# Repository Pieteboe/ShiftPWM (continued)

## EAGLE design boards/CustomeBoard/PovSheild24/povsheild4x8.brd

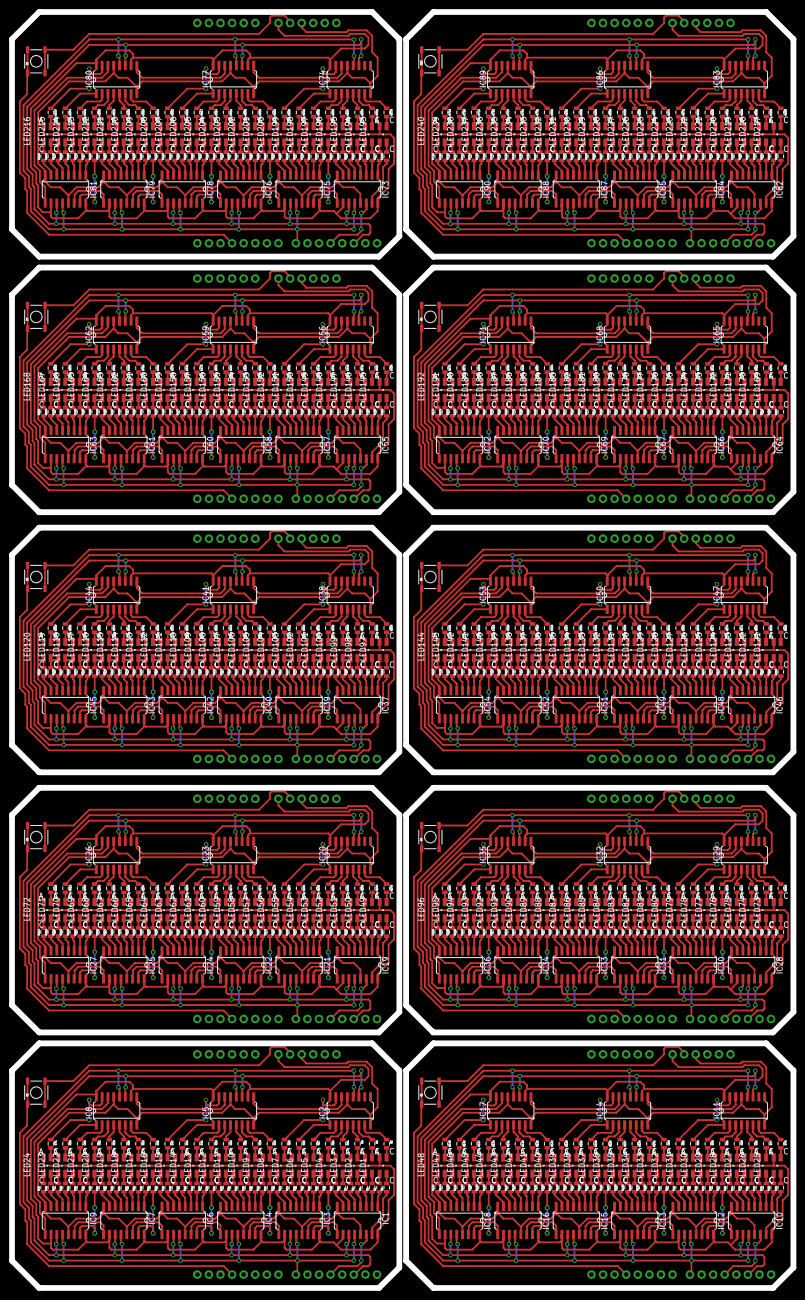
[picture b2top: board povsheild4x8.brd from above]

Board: 2 copper layers, 171.2 x 279.6 mm, 1070 parts (0 on the bottom side), 1580 nets.

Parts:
IC1, IC2, IC3, IC4, IC5, IC6, IC7, IC8, IC9, IC10, IC11, IC12, IC13, IC14, IC15, IC16, IC17, IC18, IC19, IC20, IC21, IC22, IC23, IC24, IC25, IC26, IC27, IC28, IC29, IC30, IC31, IC32, IC33, IC34, IC35, IC36, IC37, IC38, IC39, IC40, IC41, IC42, IC43, IC44, IC45, IC46, IC47, IC48, IC49, IC50, IC51, IC52, IC53, IC54, IC55, IC56, IC57, IC58, IC59, IC60, IC61, IC62, IC63, IC64, IC65, IC66, IC67, IC68, IC69, IC70, IC71, IC72, IC73, IC74, IC75, IC76, IC77, IC78, IC79, IC80, IC81, IC82, IC83, IC84, IC85, IC86, IC87, IC88, IC89, IC90: 74HC595D; SO16
LED1, LED2, LED3, LED4, LED5, LED6, LED7, LED8, LED9, LED10, LED11, LED12, LED13, LED14, LED15, LED16, LED17, LED18, LED19, LED20, LED21, LED22, LED23, LED24, LED25, LED26, LED27, LED28, LED29, LED30, LED31, LED32, LED33, LED34, LED35, LED36, LED37, LED38, LED39, LED40, LED41, LED42, LED43, LED44, LED45, LED46, LED47, LED48, LED49, LED50, LED51, LED52, LED53, LED54, LED55, LED56, LED57, LED58, LED59, LED60, LED61, LED62, LED63, LED64, LED65, LED66, LED67, LED68, LED69, LED70, LED71, LED72, LED73, LED74, LED75, LED76, LED77, LED78, LED79, LED80, LED81, LED82, LED83, LED84, LED85, LED86, LED87, LED88, LED89, LED90, LED91, LED92, LED93, LED94, LED95, LED96, LED97, LED98, LED99, LED100, LED101, LED102, LED103, LED104, LED105, LED106, LED107, LED108, LED109, LED110, LED111, LED112, LED113, LED114, LED115, LED116, LED117, LED118, LED119, LED120, LED121, LED122, LED123, LED124, LED125, LED126, LED127, LED128, LED129, LED130, LED131, LED132, LED133, LED134, LED135, LED136, LED137, LED138, LED139, LED140, LED141, LED142, LED143, LED144, LED145, LED146, LED147, LED148, LED149, LED150, LED151, LED152, LED153, LED154, LED155, LED156, LED157, LED158, LED159, LED160, LED161, LED162, LED163, LED164, LED165, LED166, LED167, LED168, LED169, LED170, LED171, LED172, LED173, LED174, LED175, LED176, LED177, LED178, LED179, LED180, LED181, LED182, LED183, LED184, LED185, LED186, LED187, LED188, LED189, LED190, LED191, LED192, LED193, LED194, LED195, LED196, LED197, LED198, LED199, LED200, LED201, LED202, LED203, LED204, LED205, LED206, LED207, LED208, LED209, LED210, LED211, LED212, LED213, LED214, LED215, LED216, LED217, LED218, LED219, LED220, LED221, LED222, LED223, LED224, LED225, LED226, LED227, LED228, LED229, LED230, LED231, LED232, LED233, LED234, LED235, LED236, LED237, LED238, LED239, LED240: P-LCC-4
R1, R2, R3, R4, R5, R6, R7, R8, R9, R10, R11, R12, R13, R14, R15, R16, R17, R18, R19, R20, R21, R22, R23, R24, R25, R26, R27, R28, R29, R30, R31, R32, R33, R34, R35, R36, R37, R38, R39, R40, R41, R42, R43, R44, R45, R46, R47, R48, R49, R50, R51, R52, R53, R54, R55, R56, R57, R58, R59, R60, R61, R62, R63, R64, R65, R66, R67, R68, R69, R70, R71, R72, R73, R74, R75, R76, R77, R78, R79, R80, R81, R82, R83, R84, R85, R86, R87, R88, R89, R90, R91, R92, R93, R94, R95, R96, R97, R98, R99, R100, R101, R102, R103, R104, R105, R106, R107, R108, R109, R110, R111, R112, R113, R114, R115, R116, R117, R118, R119, R120, R121, R122, R123, R124, R125, R126, R127, R128, R129, R130, R131, R132, R133, R134, R135, R136, R137, R138, R139, R140, R141, R142, R143, R144, R145, R146, R147, R148, R149, R150, R151, R152, R153, R154, R155, R156, R157, R158, R159, R160, R161, R162, R163, R164, R165, R166, R167, R168, R169, R170, R171, R172, R173, R174, R175, R176, R177, R178, R179, R180, R181, R182, R183, R184, R185, R186, R187, R188, R189, R190, R191, R192, R193, R194, R195, R196, R197, R198, R199, R200, R201, R202, R203, R204, R205, R206, R207, R208, R209, R210, R211, R212, R213, R214, R215, R216, R217, R218, R219, R220, R221, R222, R223, R224, R225, R226, R227, R228, R229, R230, R231, R232, R233, R234, R235, R236, R237, R238, R239, R240, R241, R242, R243, R244, R245, R246, R247, R248, R249, R250, R251, R252, R253, R254, R255, R256, R257, R258, R259, R260, R261, R262, R263, R264, R265, R266, R267, R268, R269, R270, R271, R272, R273, R274, R275, R276, R277, R278, R279, R280, R281, R282, R283, R284, R285, R286, R287, R288, R289, R290, R291, R292, R293, R294, R295, R296, R297, R298, R299, R300, R301, R302, R303, R304, R305, R306, R307, R308, R309, R310, R311, R312, R313, R314, R315, R316, R317, R318, R319, R320, R321, R322, R323, R324, R325, R326, R327, R328, R329, R330, R331, R332, R333, R334, R335, R336, R337, R338, R339, R340, R341, R342, R343, R344, R345, R346, R347, R348, R349, R350, R351, R352, R353, R354, R355, R356, R357, R358, R359, R360, R361, R362, R363, R364, R365, R366, R367, R368, R369, R370, R371, R372, R373, R374, R375, R376, R377, R378, R379, R380, R381, R382, R383, R384, R385, R386, R387, R388, R389, R390, R391, R392, R393, R394, R395, R396, R397, R398, R399, R400, R401, R402, R403, R404, R405, R406, R407, R408, R409, R410, R411, R412, R413, R414, R415, R416, R417, R418, R419, R420, R421, R422, R423, R424, R425, R426, R427, R428, R429, R430, R431, R432, R433, R434, R435, R436, R437, R438, R439, R440, R441, R442, R443, R444, R445, R446, R447, R448, R449, R450, R451, R452, R453, R454, R455, R456, R457, R458, R459, R460, R461, R462, R463, R464, R465, R466, R467, R468, R469, R470, R471, R472, R473, R474, R475, R476, R477, R478, R479, R480, R481, R482, R483, R484, R485, R486, R487, R488, R489, R490, R491, R492, R493, R494, R495, R496, R497, R498, R499, R500, R501, R502, R503, R504, R505, R506, R507, R508, R509, R510, R511, R512, R513, R514, R515, R516, R517, R518, R519, R520, R521, R522, R523, R524, R525, R526, R527, R528, R529, R530, R531, R532, R533, R534, R535, R536, R537, R538, R539, R540, R541, R542, R543, R544, R545, R546, R547, R548, R549, R550, R551, R552, R553, R554, R555, R556, R557, R558, R559, R560, R561, R562, R563, R564, R565, R566, R567, R568, R569, R570, R571, R572, R573, R574, R575, R576, R577, R578, R579, R580, R581, R582, R583, R584, R585, R586, R587, R588, R589, R590, R591, R592, R593, R594, R595, R596, R597, R598, R599, R600, R601, R602, R603, R604, R605, R606, R607, R608, R609, R610, R611, R612, R613, R614, R615, R616, R617, R618, R619, R620, R621, R622, R623, R624, R625, R626, R627, R628, R629, R630, R631, R632, R633, R634, R635, R636, R637, R638, R639, R640, R641, R642, R643, R644, R645, R646, R647, R648, R649, R650, R651, R652, R653, R654, R655, R656, R657, R658, R659, R660, R661, R662, R663, R664, R665, R666, R667, R668, R669, R670, R671, R672, R673, R674, R675, R676, R677, R678, R679, R680, R681, R682, R683, R684, R685, R686, R687, R688, R689, R690, R691, R692, R693, R694, R695, R696, R697, R698, R699, R700, R701, R702, R703, R704, R705, R706, R707, R708, R709, R710, R711, R712, R713, R714, R715, R716, R717, R718, R719, R720: 0805
S1, S2, S3, S4, S5, S6, S7, S8, S9, S10: TACTILE_SWITCH_SMD
U1, U2, U3, U4, U5, U6, U7, U8, U9, U10: ARDUINO_SHIELDNO_SILK; DUEMILANOVE_VIAS

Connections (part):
GND: IC1.8, IC1.13, IC2.8, IC2.13, IC3.8, IC3.13, IC4.8, IC4.13, IC5.8, IC5.13, IC6.8, IC6.13, IC7.8, IC7.13, IC8.8, IC8.13, IC9.8, IC9.13, S2.3, S2.4, U1.GND@0, U1.GND@1
GND1: IC10.8, IC10.13, IC11.8, IC11.13, IC12.8, IC12.13, IC13.8, IC13.13, IC14.8, IC14.13, IC15.8, IC15.13, IC16.8, IC16.13, IC17.8, IC17.13, IC18.8, IC18.13, S1.3, S1.4, U2.GND@0, U2.GND@1
GND2: IC19.8, IC19.13, IC20.8, IC20.13, IC21.8, IC21.13, IC22.8, IC22.13, IC23.8, IC23.13, IC24.8, IC24.13, IC25.8, IC25.13, IC26.8, IC26.13, IC27.8, IC27.13, S3.3, S3.4, U3.GND@0, U3.GND@1
GND3: IC28.8, IC28.13, IC29.8, IC29.13, IC30.8, IC30.13, IC31.8, IC31.13, IC32.8, IC32.13, IC33.8, IC33.13, IC34.8, IC34.13, IC35.8, IC35.13, IC36.8, IC36.13, S4.3, S4.4, U4.GND@0, U4.GND@1
GND4: IC37.8, IC37.13, IC38.8, IC38.13, IC39.8, IC39.13, IC40.8, IC40.13, IC41.8, IC41.13, IC42.8, IC42.13, IC43.8, IC43.13, IC44.8, IC44.13, IC45.8, IC45.13, S5.3, S5.4, U5.GND@0, U5.GND@1
GND5: IC46.8, IC46.13, IC47.8, IC47.13, IC48.8, IC48.13, IC49.8, IC49.13, IC50.8, IC50.13, IC51.8, IC51.13, IC52.8, IC52.13, IC53.8, IC53.13, IC54.8, IC54.13, S6.3, S6.4, U6.GND@0, U6.GND@1
GND6: IC55.8, IC55.13, IC56.8, IC56.13, IC57.8, IC57.13, IC58.8, IC58.13, IC59.8, IC59.13, IC60.8, IC60.13, IC61.8, IC61.13, IC62.8, IC62.13, IC63.8, IC63.13, S7.3, S7.4, U7.GND@0, U7.GND@1
GND7: IC64.8, IC64.13, IC65.8, IC65.13, IC66.8, IC66.13, IC67.8, IC67.13, IC68.8, IC68.13, IC69.8, IC69.13, IC70.8, IC70.13, IC71.8, IC71.13, IC72.8, IC72.13, S8.3, S8.4, U8.GND@0, U8.GND@1
GND8: IC73.8, IC73.13, IC74.8, IC74.13, IC75.8, IC75.13, IC76.8, IC76.13, IC77.8, IC77.13, IC78.8, IC78.13, IC79.8, IC79.13, IC80.8, IC80.13, IC81.8, IC81.13, S9.3, S9.4, U9.GND@0, U9.GND@1
GND9: IC82.8, IC82.13, IC83.8, IC83.13, IC84.8, IC84.13, IC85.8, IC85.13, IC86.8, IC86.13, IC87.8, IC87.13, IC88.8, IC88.13, IC89.8, IC89.13, IC90.8, IC90.13, S10.3, S10.4, U10.GND@0, U10.GND@1
LATCH: IC1.12, IC2.12, IC3.12, IC4.12, IC5.12, IC6.12, IC7.12, IC8.12, IC9.12, U1.D8
LATCH1: IC10.12, IC11.12, IC12.12, IC13.12, IC14.12, IC15.12, IC16.12, IC17.12, IC18.12, U2.D8
LATCH2: IC19.12, IC20.12, IC21.12, IC22.12, IC23.12, IC24.12, IC25.12, IC26.12, IC27.12, U3.D8
LATCH3: IC28.12, IC29.12, IC30.12, IC31.12, IC32.12, IC33.12, IC34.12, IC35.12, IC36.12, U4.D8
LATCH4: IC37.12, IC38.12, IC39.12, IC40.12, IC41.12, IC42.12, IC43.12, IC44.12, IC45.12, U5.D8
LATCH5: IC46.12, IC47.12, IC48.12, IC49.12, IC50.12, IC51.12, IC52.12, IC53.12, IC54.12, U6.D8
LATCH6: IC55.12, IC56.12, IC57.12, IC58.12, IC59.12, IC60.12, IC61.12, IC62.12, IC63.12, U7.D8
LATCH7: IC64.12, IC65.12, IC66.12, IC67.12, IC68.12, IC69.12, IC70.12, IC71.12, IC72.12, U8.D8
LATCH8: IC73.12, IC74.12, IC75.12, IC76.12, IC77.12, IC78.12, IC79.12, IC80.12, IC81.12, U9.D8
LATCH9: IC82.12, IC83.12, IC84.12, IC85.12, IC86.12, IC87.12, IC88.12, IC89.12, IC90.12, U10.D8
unnamed: IC1.15, R3.1
unnamed: IC1.1, R1.1
unnamed: IC1.2, R6.1
unnamed: IC1.3, R4.1
unnamed: IC1.4, R9.1
unnamed: IC1.5, R7.1
unnamed: IC1.6, R12.1
unnamed: IC1.7, R10.1
unnamed: LED1.C@1, R1.2
unnamed: LED1.C@3, R2.2
unnamed: LED1.C@4, R3.2
unnamed: LED2.C@1, R4.2
unnamed: LED2.C@3, R5.2
unnamed: LED2.C@4, R6.2
unnamed: LED3.C@1, R7.2
unnamed: LED3.C@3, R8.2
unnamed: LED3.C@4, R9.2
unnamed: LED4.C@1, R10.2
unnamed: IC3.15, R15.1
unnamed: IC3.1, R13.1
unnamed: LED4.C@3, R11.2
unnamed: IC3.2, R18.1
unnamed: IC3.3, R16.1
unnamed: IC3.4, R21.1
unnamed: IC3.5, R19.1
unnamed: IC3.6, R24.1
unnamed: IC3.7, R22.1
unnamed: LED4.C@4, R12.2
unnamed: LED5.C@1, R13.2
unnamed: LED5.C@3, R14.2
unnamed: LED5.C@4, R15.2
unnamed: LED6.C@1, R16.2
unnamed: LED6.C@3, R17.2
unnamed: LED6.C@4, R18.2
unnamed: IC2.15, R23.1
unnamed: IC2.1, R20.1
unnamed: LED7.C@1, R19.2
unnamed: IC2.2, R17.1
unnamed: LED7.C@3, R20.2
unnamed: IC2.3, R14.1
unnamed: LED7.C@4, R21.2
unnamed: IC2.4, R11.1
unnamed: IC2.5, R8.1
unnamed: IC2.6, R5.1
unnamed: IC2.7, R2.1
unnamed: LED8.C@1, R22.2
unnamed: LED8.C@3, R23.2
unnamed: LED8.C@4, R24.2
unnamed: IC4.15, R27.1
unnamed: IC4.1, R25.1
unnamed: IC4.2, R30.1
unnamed: IC4.3, R28.1
unnamed: IC4.4, R33.1
unnamed: IC4.5, R31.1
unnamed: IC4.6, R36.1
unnamed: IC4.7, R34.1
unnamed: LED9.C@1, R25.2
unnamed: LED9.C@3, R26.2
unnamed: LED9.C@4, R27.2
unnamed: LED10.C@1, R28.2
unnamed: LED10.C@3, R29.2
unnamed: LED10.C@4, R30.2
unnamed: LED11.C@1, R31.2
unnamed: LED11.C@3, R32.2
unnamed: LED11.C@4, R33.2
unnamed: LED12.C@1, R34.2
unnamed: IC5.15, R47.1
unnamed: IC5.1, R44.1
unnamed: LED12.C@3, R35.2
unnamed: IC5.2, R41.1
unnamed: IC5.3, R38.1
unnamed: IC5.4, R35.1
unnamed: IC5.5, R32.1
unnamed: IC5.6, R29.1
unnamed: IC5.7, R26.1
unnamed: LED12.C@4, R36.2
unnamed: LED13.C@1, R37.2
unnamed: LED13.C@3, R38.2
unnamed: LED13.C@4, R39.2
unnamed: LED14.C@1, R40.2
unnamed: LED14.C@3, R41.2
unnamed: LED14.C@4, R42.2
unnamed: IC6.15, R39.1
unnamed: IC6.1, R37.1
unnamed: LED15.C@1, R43.2
unnamed: IC6.2, R42.1
unnamed: LED15.C@3, R44.2
unnamed: IC6.3, R40.1
unnamed: LED15.C@4, R45.2
unnamed: IC6.4, R45.1
unnamed: IC6.5, R43.1
unnamed: IC6.6, R48.1
unnamed: IC6.7, R46.1
unnamed: LED16.C@1, R46.2
unnamed: LED16.C@3, R47.2
unnamed: LED16.C@4, R48.2
unnamed: LED25.C@1, R73.2
unnamed: LED25.C@3, R74.2
unnamed: LED25.C@4, R75.2
unnamed: LED26.C@1, R76.2
unnamed: LED26.C@3, R77.2
unnamed: LED26.C@4, R78.2
unnamed: LED27.C@1, R79.2
unnamed: LED27.C@3, R80.2
unnamed: LED17.C@1, R49.2
unnamed: LED17.C@3, R50.2
unnamed: LED17.C@4, R51.2
unnamed: LED18.C@1, R52.2
unnamed: LED18.C@3, R53.2
unnamed: LED18.C@4, R54.2
unnamed: LED19.C@1, R55.2
unnamed: LED19.C@3, R56.2
unnamed: LED19.C@4, R57.2
unnamed: LED20.C@1, R58.2
unnamed: LED27.C@4, R81.2
unnamed: LED28.C@1, R82.2
unnamed: LED20.C@3, R59.2
unnamed: LED28.C@3, R83.2
unnamed: LED28.C@4, R84.2
unnamed: LED29.C@1, R85.2
unnamed: LED29.C@3, R86.2
unnamed: LED29.C@4, R87.2
unnamed: LED30.C@1, R88.2
unnamed: LED20.C@4, R60.2
unnamed: LED21.C@1, R61.2
unnamed: LED21.C@3, R62.2
unnamed: LED21.C@4, R63.2
unnamed: LED22.C@1, R64.2
unnamed: LED22.C@3, R65.2
unnamed: LED22.C@4, R66.2
unnamed: LED30.C@3, R89.2
unnamed: LED30.C@4, R90.2
unnamed: LED23.C@1, R67.2
unnamed: LED31.C@1, R91.2
unnamed: LED23.C@3, R68.2
unnamed: LED31.C@3, R92.2
unnamed: LED23.C@4, R69.2
unnamed: LED31.C@4, R93.2
unnamed: LED32.C@1, R94.2
unnamed: LED32.C@3, R95.2
unnamed: LED32.C@4, R96.2
unnamed: LED24.C@1, R70.2
unnamed: LED24.C@3, R71.2
unnamed: LED24.C@4, R72.2
unnamed: IC7.15, R51.1
unnamed: IC7.1, R49.1
unnamed: IC7.2, R54.1
unnamed: IC7.3, R52.1
unnamed: IC7.4, R57.1
unnamed: IC7.5, R55.1
unnamed: IC7.6, R60.1
unnamed: IC7.7, R58.1
unnamed: LED33.C@1, R97.2
unnamed: LED33.C@3, R98.2
unnamed: LED33.C@4, R99.2
unnamed: LED34.C@1, R100.2
unnamed: LED34.C@3, R101.2
unnamed: LED34.C@4, R102.2
unnamed: LED35.C@1, R103.2
unnamed: LED35.C@3, R104.2
unnamed: LED35.C@4, R105.2
unnamed: LED36.C@1, R106.2
unnamed: IC8.15, R71.1
unnamed: IC8.1, R68.1
unnamed: LED36.C@3, R107.2
unnamed: IC8.2, R65.1
unnamed: IC8.3, R62.1
unnamed: IC8.4, R59.1
unnamed: IC8.5, R56.1
unnamed: IC8.6, R53.1
unnamed: IC8.7, R50.1
unnamed: LED36.C@4, R108.2
unnamed: LED37.C@1, R109.2
unnamed: LED37.C@3, R110.2
unnamed: LED37.C@4, R111.2
unnamed: LED38.C@1, R112.2
unnamed: LED38.C@3, R113.2
unnamed: LED38.C@4, R114.2
unnamed: IC9.15, R63.1
unnamed: IC9.1, R61.1
unnamed: LED39.C@1, R115.2
unnamed: IC9.2, R66.1
unnamed: LED39.C@3, R116.2
unnamed: IC9.3, R64.1
unnamed: LED39.C@4, R117.2
unnamed: IC9.4, R69.1
unnamed: IC9.5, R67.1
unnamed: IC9.6, R72.1
unnamed: IC9.7, R70.1
unnamed: LED40.C@1, R118.2
unnamed: LED40.C@3, R119.2
unnamed: LED40.C@4, R120.2
unnamed: IC1.9, IC3.14
unnamed: IC3.9, IC4.14
unnamed: IC4.9, IC6.14
unnamed: IC6.9, IC7.14
unnamed: IC7.9, IC9.14
unnamed: LED41.C@1, R121.2
unnamed: LED41.C@3, R122.2
unnamed: LED41.C@4, R123.2
unnamed: IC2.14, IC5.9
unnamed: IC5.14, IC8.9
unnamed: IC8.14, IC9.9
unnamed: LED42.C@1, R124.2
unnamed: IC1.14, U1.D11
unnamed: S2.1, S2.2, U1.D3
unnamed: LED42.C@3, R125.2
unnamed: LED42.C@4, R126.2
unnamed: LED43.C@1, R127.2
unnamed: LED43.C@3, R128.2
unnamed: LED43.C@4, R129.2
unnamed: LED44.C@1, R130.2
unnamed: LED44.C@3, R131.2
unnamed: LED44.C@4, R132.2
unnamed: LED45.C@1, R133.2
unnamed: LED45.C@3, R134.2
unnamed: LED45.C@4, R135.2
unnamed: LED46.C@1, R136.2
unnamed: LED46.C@3, R137.2
unnamed: LED46.C@4, R138.2
unnamed: LED47.C@1, R139.2
unnamed: LED47.C@3, R140.2
unnamed: LED47.C@4, R141.2
unnamed: LED48.C@1, R142.2
unnamed: LED48.C@3, R143.2
unnamed: LED48.C@4, R144.2
unnamed: IC10.15, R75.1
unnamed: IC10.1, R73.1
unnamed: IC10.2, R78.1
unnamed: IC10.3, R76.1
unnamed: IC10.4, R81.1
unnamed: IC10.5, R79.1
unnamed: IC10.6, R84.1
unnamed: IC10.7, R82.1
unnamed: IC12.15, R87.1
unnamed: IC12.1, R85.1
unnamed: IC12.2, R90.1
unnamed: IC12.3, R88.1
unnamed: IC12.4, R93.1
unnamed: IC12.5, R91.1
unnamed: IC12.6, R96.1
unnamed: IC12.7, R94.1
unnamed: IC11.15, R95.1
unnamed: IC11.1, R92.1
unnamed: IC11.2, R89.1
unnamed: IC11.3, R86.1
unnamed: IC11.4, R83.1
unnamed: IC11.5, R80.1
unnamed: IC11.6, R77.1
unnamed: IC11.7, R74.1
unnamed: IC13.15, R99.1
unnamed: IC13.1, R97.1
unnamed: IC13.2, R102.1
unnamed: IC13.3, R100.1
unnamed: IC13.4, R105.1
unnamed: IC13.5, R103.1
unnamed: IC13.6, R108.1
unnamed: IC13.7, R106.1
unnamed: IC14.15, R119.1
unnamed: IC14.1, R116.1
unnamed: IC14.2, R113.1
unnamed: IC14.3, R110.1
unnamed: IC14.4, R107.1
unnamed: IC14.5, R104.1
unnamed: IC14.6, R101.1
unnamed: IC14.7, R98.1
unnamed: IC15.15, R111.1
unnamed: IC15.1, R109.1
unnamed: IC15.2, R114.1
unnamed: IC15.3, R112.1
unnamed: IC15.4, R117.1
unnamed: IC15.5, R115.1
unnamed: IC15.6, R120.1
unnamed: IC15.7, R118.1
unnamed: IC16.15, R123.1
unnamed: IC16.1, R121.1
unnamed: IC16.2, R126.1
unnamed: IC16.3, R124.1
unnamed: IC16.4, R129.1
unnamed: IC16.5, R127.1
unnamed: IC16.6, R132.1
unnamed: IC16.7, R130.1
unnamed: IC18.15, R135.1
unnamed: IC18.1, R133.1
unnamed: IC18.2, R138.1
unnamed: IC18.3, R136.1
unnamed: IC18.4, R141.1
unnamed: IC18.5, R139.1
unnamed: IC18.6, R144.1
unnamed: IC18.7, R142.1
unnamed: IC17.15, R143.1
unnamed: IC17.1, R140.1
unnamed: IC17.2, R137.1
unnamed: IC17.3, R134.1
unnamed: IC17.4, R131.1
unnamed: IC17.5, R128.1
unnamed: IC17.6, R125.1
unnamed: IC17.7, R122.1
unnamed: IC10.9, IC12.14
unnamed: IC12.9, IC13.14
unnamed: IC13.9, IC15.14
unnamed: IC15.9, IC16.14
unnamed: IC16.9, IC18.14
unnamed: IC17.14, IC18.9
unnamed: IC14.14, IC17.9
unnamed: IC11.14, IC14.9
unnamed: IC10.14, U2.D11
unnamed: S1.1, S1.2, U2.D3
unnamed: LED49.C@1, R145.2
unnamed: LED49.C@3, R146.2
unnamed: LED49.C@4, R147.2
unnamed: LED50.C@1, R148.2
unnamed: LED50.C@3, R149.2
unnamed: LED50.C@4, R150.2
unnamed: LED51.C@1, R151.2
unnamed: LED51.C@3, R152.2
unnamed: LED51.C@4, R153.2
unnamed: LED52.C@1, R154.2
unnamed: LED52.C@3, R155.2
unnamed: LED52.C@4, R156.2
unnamed: LED53.C@1, R157.2
unnamed: LED53.C@3, R158.2
unnamed: LED53.C@4, R159.2
unnamed: LED54.C@1, R160.2
unnamed: LED54.C@3, R161.2
unnamed: LED54.C@4, R162.2
unnamed: LED55.C@1, R163.2
unnamed: LED55.C@3, R164.2
unnamed: LED55.C@4, R165.2
unnamed: LED56.C@1, R166.2
unnamed: LED56.C@3, R167.2
unnamed: LED56.C@4, R168.2
unnamed: LED57.C@1, R169.2
unnamed: LED57.C@3, R170.2
unnamed: LED57.C@4, R171.2
unnamed: LED58.C@1, R172.2
unnamed: LED58.C@3, R173.2
unnamed: LED58.C@4, R174.2
unnamed: LED59.C@1, R175.2
unnamed: LED59.C@3, R176.2
unnamed: LED59.C@4, R177.2
unnamed: LED60.C@1, R178.2
unnamed: LED60.C@3, R179.2
unnamed: LED60.C@4, R180.2
unnamed: LED61.C@1, R181.2
unnamed: LED61.C@3, R182.2
unnamed: LED61.C@4, R183.2
unnamed: LED62.C@1, R184.2
unnamed: LED62.C@3, R185.2
unnamed: LED62.C@4, R186.2
unnamed: LED63.C@1, R187.2
unnamed: LED63.C@3, R188.2
unnamed: LED63.C@4, R189.2
unnamed: LED64.C@1, R190.2
unnamed: LED64.C@3, R191.2
unnamed: LED64.C@4, R192.2
unnamed: LED65.C@1, R193.2
unnamed: LED65.C@3, R194.2
unnamed: LED65.C@4, R195.2
unnamed: LED66.C@1, R196.2
unnamed: LED66.C@3, R197.2
unnamed: LED66.C@4, R198.2
unnamed: LED67.C@1, R199.2
unnamed: LED67.C@3, R200.2
unnamed: LED67.C@4, R201.2
unnamed: LED68.C@1, R202.2
unnamed: LED68.C@3, R203.2
unnamed: LED68.C@4, R204.2
unnamed: LED69.C@1, R205.2
unnamed: LED69.C@3, R206.2
unnamed: LED69.C@4, R207.2
unnamed: LED70.C@1, R208.2
unnamed: LED70.C@3, R209.2
unnamed: LED70.C@4, R210.2
unnamed: LED71.C@1, R211.2
unnamed: LED71.C@3, R212.2
unnamed: LED71.C@4, R213.2
unnamed: LED72.C@1, R214.2
unnamed: LED72.C@3, R215.2
unnamed: LED72.C@4, R216.2
unnamed: IC19.15, R147.1
unnamed: IC19.1, R145.1
unnamed: IC19.2, R150.1
unnamed: IC19.3, R148.1
unnamed: IC19.4, R153.1
unnamed: IC19.5, R151.1
unnamed: IC19.6, R156.1
unnamed: IC19.7, R154.1
unnamed: IC21.15, R159.1
unnamed: IC21.1, R157.1
unnamed: IC21.2, R162.1
unnamed: IC21.3, R160.1
unnamed: IC21.4, R165.1
unnamed: IC21.5, R163.1
unnamed: IC21.6, R168.1
unnamed: IC21.7, R166.1
unnamed: IC20.15, R167.1
unnamed: IC20.1, R164.1
unnamed: IC20.2, R161.1
unnamed: IC20.3, R158.1
unnamed: IC20.4, R155.1
unnamed: IC20.5, R152.1
unnamed: IC20.6, R149.1
unnamed: IC20.7, R146.1
unnamed: IC22.15, R171.1
unnamed: IC22.1, R169.1
unnamed: IC22.2, R174.1
unnamed: IC22.3, R172.1
unnamed: IC22.4, R177.1
unnamed: IC22.5, R175.1
unnamed: IC22.6, R180.1
unnamed: IC22.7, R178.1
unnamed: IC23.15, R191.1
unnamed: IC23.1, R188.1
unnamed: IC23.2, R185.1
unnamed: IC23.3, R182.1
unnamed: IC23.4, R179.1
unnamed: IC23.5, R176.1
unnamed: IC23.6, R173.1
unnamed: IC23.7, R170.1
unnamed: IC24.15, R183.1
unnamed: IC24.1, R181.1
unnamed: IC24.2, R186.1
unnamed: IC24.3, R184.1
unnamed: IC24.4, R189.1
unnamed: IC24.5, R187.1
unnamed: IC24.6, R192.1
unnamed: IC24.7, R190.1
unnamed: IC25.15, R195.1
unnamed: IC25.1, R193.1
unnamed: IC25.2, R198.1
unnamed: IC25.3, R196.1
unnamed: IC25.4, R201.1
unnamed: IC25.5, R199.1
unnamed: IC25.6, R204.1
unnamed: IC25.7, R202.1
unnamed: IC27.15, R207.1
unnamed: IC27.1, R205.1
unnamed: IC27.2, R210.1
unnamed: IC27.3, R208.1
unnamed: IC27.4, R213.1
unnamed: IC27.5, R211.1
unnamed: IC27.6, R216.1
unnamed: IC27.7, R214.1
unnamed: IC26.15, R215.1
unnamed: IC26.1, R212.1
unnamed: IC26.2, R209.1
unnamed: IC26.3, R206.1
unnamed: IC26.4, R203.1
unnamed: IC26.5, R200.1
unnamed: IC26.6, R197.1
unnamed: IC26.7, R194.1
unnamed: IC19.9, IC21.14
unnamed: IC21.9, IC22.14
unnamed: IC22.9, IC24.14
unnamed: IC24.9, IC25.14
unnamed: IC25.9, IC27.14
unnamed: IC26.14, IC27.9
unnamed: IC23.14, IC26.9
unnamed: IC20.14, IC23.9
unnamed: IC19.14, U3.D11
unnamed: S3.1, S3.2, U3.D3
unnamed: LED73.C@1, R217.2
unnamed: LED73.C@3, R218.2
unnamed: LED73.C@4, R219.2
unnamed: LED74.C@1, R220.2
unnamed: LED74.C@3, R221.2
unnamed: LED74.C@4, R222.2
unnamed: LED75.C@1, R223.2
unnamed: LED75.C@3, R224.2
unnamed: LED75.C@4, R225.2
unnamed: LED76.C@1, R226.2
unnamed: LED76.C@3, R227.2
unnamed: LED76.C@4, R228.2
unnamed: LED77.C@1, R229.2
unnamed: LED77.C@3, R230.2
unnamed: LED77.C@4, R231.2
unnamed: LED78.C@1, R232.2
unnamed: LED78.C@3, R233.2
unnamed: LED78.C@4, R234.2
unnamed: LED79.C@1, R235.2
unnamed: LED79.C@3, R236.2
unnamed: LED79.C@4, R237.2
unnamed: LED80.C@1, R238.2
unnamed: LED80.C@3, R239.2
unnamed: LED80.C@4, R240.2
unnamed: LED81.C@1, R241.2
unnamed: LED81.C@3, R242.2
unnamed: LED81.C@4, R243.2
unnamed: LED82.C@1, R244.2
unnamed: LED82.C@3, R245.2
unnamed: LED82.C@4, R246.2
unnamed: LED83.C@1, R247.2
unnamed: LED83.C@3, R248.2
unnamed: LED83.C@4, R249.2
unnamed: LED84.C@1, R250.2
unnamed: LED84.C@3, R251.2
unnamed: LED84.C@4, R252.2
unnamed: LED85.C@1, R253.2
unnamed: LED85.C@3, R254.2
unnamed: LED85.C@4, R255.2
unnamed: LED86.C@1, R256.2
unnamed: LED86.C@3, R257.2
unnamed: LED86.C@4, R258.2
unnamed: LED87.C@1, R259.2
unnamed: LED87.C@3, R260.2
unnamed: LED87.C@4, R261.2
unnamed: LED88.C@1, R262.2
unnamed: LED88.C@3, R263.2
unnamed: LED88.C@4, R264.2
unnamed: LED89.C@1, R265.2
unnamed: LED89.C@3, R266.2
unnamed: LED89.C@4, R267.2
unnamed: LED90.C@1, R268.2
unnamed: LED90.C@3, R269.2
unnamed: LED90.C@4, R270.2
unnamed: LED91.C@1, R271.2
unnamed: LED91.C@3, R272.2
unnamed: LED91.C@4, R273.2
unnamed: LED92.C@1, R274.2
unnamed: LED92.C@3, R275.2
unnamed: LED92.C@4, R276.2
unnamed: LED93.C@1, R277.2
unnamed: LED93.C@3, R278.2
unnamed: LED93.C@4, R279.2
unnamed: LED94.C@1, R280.2
unnamed: LED94.C@3, R281.2
unnamed: LED94.C@4, R282.2
unnamed: LED95.C@1, R283.2
unnamed: LED95.C@3, R284.2
unnamed: LED95.C@4, R285.2
unnamed: LED96.C@1, R286.2
unnamed: LED96.C@3, R287.2
unnamed: LED96.C@4, R288.2
unnamed: IC28.15, R219.1
unnamed: IC28.1, R217.1
unnamed: IC28.2, R222.1
unnamed: IC28.3, R220.1
unnamed: IC28.4, R225.1
unnamed: IC28.5, R223.1
unnamed: IC28.6, R228.1
unnamed: IC28.7, R226.1
unnamed: IC30.15, R231.1
unnamed: IC30.1, R229.1
unnamed: IC30.2, R234.1
unnamed: IC30.3, R232.1
unnamed: IC30.4, R237.1
unnamed: IC30.5, R235.1
unnamed: IC30.6, R240.1
unnamed: IC30.7, R238.1
unnamed: IC29.15, R239.1
unnamed: IC29.1, R236.1
unnamed: IC29.2, R233.1
unnamed: IC29.3, R230.1
unnamed: IC29.4, R227.1
unnamed: IC29.5, R224.1
unnamed: IC29.6, R221.1
unnamed: IC29.7, R218.1
unnamed: IC31.15, R243.1
unnamed: IC31.1, R241.1
unnamed: IC31.2, R246.1
unnamed: IC31.3, R244.1
unnamed: IC31.4, R249.1
unnamed: IC31.5, R247.1
unnamed: IC31.6, R252.1
unnamed: IC31.7, R250.1
unnamed: IC32.15, R263.1
unnamed: IC32.1, R260.1
unnamed: IC32.2, R257.1
unnamed: IC32.3, R254.1
unnamed: IC32.4, R251.1
unnamed: IC32.5, R248.1
unnamed: IC32.6, R245.1
unnamed: IC32.7, R242.1
unnamed: IC33.15, R255.1
unnamed: IC33.1, R253.1
unnamed: IC33.2, R258.1
unnamed: IC33.3, R256.1
unnamed: IC33.4, R261.1
unnamed: IC33.5, R259.1
unnamed: IC33.6, R264.1
unnamed: IC33.7, R262.1
unnamed: IC34.15, R267.1
unnamed: IC34.1, R265.1
unnamed: IC34.2, R270.1
unnamed: IC34.3, R268.1
unnamed: IC34.4, R273.1
unnamed: IC34.5, R271.1
unnamed: IC34.6, R276.1
unnamed: IC34.7, R274.1
unnamed: IC36.15, R279.1
unnamed: IC36.1, R277.1
unnamed: IC36.2, R282.1
unnamed: IC36.3, R280.1
unnamed: IC36.4, R285.1
unnamed: IC36.5, R283.1
unnamed: IC36.6, R288.1
unnamed: IC36.7, R286.1
unnamed: IC35.15, R287.1
unnamed: IC35.1, R284.1
unnamed: IC35.2, R281.1
unnamed: IC35.3, R278.1
unnamed: IC35.4, R275.1
unnamed: IC35.5, R272.1
unnamed: IC35.6, R269.1
unnamed: IC35.7, R266.1
unnamed: IC28.9, IC30.14
unnamed: IC30.9, IC31.14
unnamed: IC31.9, IC33.14
unnamed: IC33.9, IC34.14
unnamed: IC34.9, IC36.14
unnamed: IC35.14, IC36.9
unnamed: IC32.14, IC35.9
unnamed: IC29.14, IC32.9
unnamed: IC28.14, U4.D11
unnamed: S4.1, S4.2, U4.D3
unnamed: LED97.C@1, R289.2
unnamed: LED97.C@3, R290.2
unnamed: LED97.C@4, R291.2
unnamed: LED98.C@1, R292.2
unnamed: LED98.C@3, R293.2
unnamed: LED98.C@4, R294.2
unnamed: LED99.C@1, R295.2
unnamed: LED99.C@3, R296.2
unnamed: LED99.C@4, R297.2
unnamed: LED100.C@1, R298.2
unnamed: LED100.C@3, R299.2
unnamed: LED100.C@4, R300.2
unnamed: LED101.C@1, R301.2
unnamed: LED101.C@3, R302.2
unnamed: LED101.C@4, R303.2
unnamed: LED102.C@1, R304.2
unnamed: LED102.C@3, R305.2
unnamed: LED102.C@4, R306.2
unnamed: LED103.C@1, R307.2
unnamed: LED103.C@3, R308.2
unnamed: LED103.C@4, R309.2
unnamed: LED104.C@1, R310.2
unnamed: LED104.C@3, R311.2
unnamed: LED104.C@4, R312.2
unnamed: LED105.C@1, R313.2
unnamed: LED105.C@3, R314.2
unnamed: LED105.C@4, R315.2
unnamed: LED106.C@1, R316.2
unnamed: LED106.C@3, R317.2
unnamed: LED106.C@4, R318.2
unnamed: LED107.C@1, R319.2
unnamed: LED107.C@3, R320.2
unnamed: LED107.C@4, R321.2
unnamed: LED108.C@1, R322.2
unnamed: LED108.C@3, R323.2
unnamed: LED108.C@4, R324.2
unnamed: LED109.C@1, R325.2
unnamed: LED109.C@3, R326.2
unnamed: LED109.C@4, R327.2
unnamed: LED110.C@1, R328.2
unnamed: LED110.C@3, R329.2
unnamed: LED110.C@4, R330.2
unnamed: LED111.C@1, R331.2
unnamed: LED111.C@3, R332.2
unnamed: LED111.C@4, R333.2
unnamed: LED112.C@1, R334.2
unnamed: LED112.C@3, R335.2
unnamed: LED112.C@4, R336.2
unnamed: LED113.C@1, R337.2
unnamed: LED113.C@3, R338.2
unnamed: LED113.C@4, R339.2
unnamed: LED114.C@1, R340.2
unnamed: LED114.C@3, R341.2
unnamed: LED114.C@4, R342.2
unnamed: LED115.C@1, R343.2
unnamed: LED115.C@3, R344.2
unnamed: LED115.C@4, R345.2
unnamed: LED116.C@1, R346.2
unnamed: LED116.C@3, R347.2
unnamed: LED116.C@4, R348.2
unnamed: LED117.C@1, R349.2
unnamed: LED117.C@3, R350.2
unnamed: LED117.C@4, R351.2
unnamed: LED118.C@1, R352.2
unnamed: LED118.C@3, R353.2
unnamed: LED118.C@4, R354.2
unnamed: LED119.C@1, R355.2
unnamed: LED119.C@3, R356.2
unnamed: LED119.C@4, R357.2
unnamed: LED120.C@1, R358.2
unnamed: LED120.C@3, R359.2
unnamed: LED120.C@4, R360.2
unnamed: IC37.15, R291.1
unnamed: IC37.1, R289.1
unnamed: IC37.2, R294.1
unnamed: IC37.3, R292.1
unnamed: IC37.4, R297.1
unnamed: IC37.5, R295.1
unnamed: IC37.6, R300.1
unnamed: IC37.7, R298.1
unnamed: IC39.15, R303.1
unnamed: IC39.1, R301.1
unnamed: IC39.2, R306.1
unnamed: IC39.3, R304.1
unnamed: IC39.4, R309.1
unnamed: IC39.5, R307.1
unnamed: IC39.6, R312.1
unnamed: IC39.7, R310.1
unnamed: IC38.15, R311.1
unnamed: IC38.1, R308.1
unnamed: IC38.2, R305.1
unnamed: IC38.3, R302.1
unnamed: IC38.4, R299.1
unnamed: IC38.5, R296.1
unnamed: IC38.6, R293.1
unnamed: IC38.7, R290.1
unnamed: IC40.15, R315.1
unnamed: IC40.1, R313.1
unnamed: IC40.2, R318.1
unnamed: IC40.3, R316.1
unnamed: IC40.4, R321.1
unnamed: IC40.5, R319.1
unnamed: IC40.6, R324.1
unnamed: IC40.7, R322.1
unnamed: IC41.15, R335.1
unnamed: IC41.1, R332.1
unnamed: IC41.2, R329.1
unnamed: IC41.3, R326.1
unnamed: IC41.4, R323.1
unnamed: IC41.5, R320.1
unnamed: IC41.6, R317.1
unnamed: IC41.7, R314.1
unnamed: IC42.15, R327.1
unnamed: IC42.1, R325.1
unnamed: IC42.2, R330.1
unnamed: IC42.3, R328.1
unnamed: IC42.4, R333.1
unnamed: IC42.5, R331.1
unnamed: IC42.6, R336.1
unnamed: IC42.7, R334.1
unnamed: IC43.15, R339.1
unnamed: IC43.1, R337.1
unnamed: IC43.2, R342.1
unnamed: IC43.3, R340.1
unnamed: IC43.4, R345.1
unnamed: IC43.5, R343.1
unnamed: IC43.6, R348.1
unnamed: IC43.7, R346.1
unnamed: IC45.15, R351.1
unnamed: IC45.1, R349.1
unnamed: IC45.2, R354.1
unnamed: IC45.3, R352.1
unnamed: IC45.4, R357.1
unnamed: IC45.5, R355.1
unnamed: IC45.6, R360.1
unnamed: IC45.7, R358.1
unnamed: IC44.15, R359.1
unnamed: IC44.1, R356.1
unnamed: IC44.2, R353.1
unnamed: IC44.3, R350.1
unnamed: IC44.4, R347.1
unnamed: IC44.5, R344.1
unnamed: IC44.6, R341.1
unnamed: IC44.7, R338.1
unnamed: IC37.9, IC39.14
unnamed: IC39.9, IC40.14
unnamed: IC40.9, IC42.14
unnamed: IC42.9, IC43.14
unnamed: IC43.9, IC45.14
unnamed: IC44.14, IC45.9
unnamed: IC41.14, IC44.9
unnamed: IC38.14, IC41.9
unnamed: IC37.14, U5.D11
unnamed: S5.1, S5.2, U5.D3
unnamed: LED121.C@1, R361.2
unnamed: LED121.C@3, R362.2
unnamed: LED121.C@4, R363.2
unnamed: LED122.C@1, R364.2
unnamed: LED122.C@3, R365.2
unnamed: LED122.C@4, R366.2
unnamed: LED123.C@1, R367.2
unnamed: LED123.C@3, R368.2
unnamed: LED123.C@4, R369.2
unnamed: LED124.C@1, R370.2
unnamed: LED124.C@3, R371.2
unnamed: LED124.C@4, R372.2
unnamed: LED125.C@1, R373.2
unnamed: LED125.C@3, R374.2
unnamed: LED125.C@4, R375.2
unnamed: LED126.C@1, R376.2
unnamed: LED126.C@3, R377.2
unnamed: LED126.C@4, R378.2
unnamed: LED127.C@1, R379.2
unnamed: LED127.C@3, R380.2
unnamed: LED127.C@4, R381.2
unnamed: LED128.C@1, R382.2
unnamed: LED128.C@3, R383.2
unnamed: LED128.C@4, R384.2
unnamed: LED129.C@1, R385.2
unnamed: LED129.C@3, R386.2
unnamed: LED129.C@4, R387.2
unnamed: LED130.C@1, R388.2
unnamed: LED130.C@3, R389.2
unnamed: LED130.C@4, R390.2
unnamed: LED131.C@1, R391.2
unnamed: LED131.C@3, R392.2
unnamed: LED131.C@4, R393.2
unnamed: LED132.C@1, R394.2
unnamed: LED132.C@3, R395.2
unnamed: LED132.C@4, R396.2
unnamed: LED133.C@1, R397.2
unnamed: LED133.C@3, R398.2
unnamed: LED133.C@4, R399.2
unnamed: LED134.C@1, R400.2
unnamed: LED134.C@3, R401.2
unnamed: LED134.C@4, R402.2
unnamed: LED135.C@1, R403.2
unnamed: LED135.C@3, R404.2
unnamed: LED135.C@4, R405.2
unnamed: LED136.C@1, R406.2
unnamed: LED136.C@3, R407.2
unnamed: LED136.C@4, R408.2
unnamed: LED137.C@1, R409.2
unnamed: LED137.C@3, R410.2
unnamed: LED137.C@4, R411.2
unnamed: LED138.C@1, R412.2
unnamed: LED138.C@3, R413.2
unnamed: LED138.C@4, R414.2
unnamed: LED139.C@1, R415.2
unnamed: LED139.C@3, R416.2
unnamed: LED139.C@4, R417.2
unnamed: LED140.C@1, R418.2
unnamed: LED140.C@3, R419.2
unnamed: LED140.C@4, R420.2
unnamed: LED141.C@1, R421.2
unnamed: LED141.C@3, R422.2
unnamed: LED141.C@4, R423.2
unnamed: LED142.C@1, R424.2
unnamed: LED142.C@3, R425.2
unnamed: LED142.C@4, R426.2
unnamed: LED143.C@1, R427.2
unnamed: LED143.C@3, R428.2
unnamed: LED143.C@4, R429.2
unnamed: LED144.C@1, R430.2
unnamed: LED144.C@3, R431.2
unnamed: LED144.C@4, R432.2
unnamed: IC46.15, R363.1
unnamed: IC46.1, R361.1
unnamed: IC46.2, R366.1
unnamed: IC46.3, R364.1
unnamed: IC46.4, R369.1
unnamed: IC46.5, R367.1
unnamed: IC46.6, R372.1
unnamed: IC46.7, R370.1
unnamed: IC48.15, R375.1
unnamed: IC48.1, R373.1
unnamed: IC48.2, R378.1
unnamed: IC48.3, R376.1
unnamed: IC48.4, R381.1
unnamed: IC48.5, R379.1
unnamed: IC48.6, R384.1
unnamed: IC48.7, R382.1
unnamed: IC47.15, R383.1
unnamed: IC47.1, R380.1
unnamed: IC47.2, R377.1
unnamed: IC47.3, R374.1
unnamed: IC47.4, R371.1
unnamed: IC47.5, R368.1
unnamed: IC47.6, R365.1
unnamed: IC47.7, R362.1
unnamed: IC49.15, R387.1
unnamed: IC49.1, R385.1
unnamed: IC49.2, R390.1
unnamed: IC49.3, R388.1
unnamed: IC49.4, R393.1
unnamed: IC49.5, R391.1
unnamed: IC49.6, R396.1
unnamed: IC49.7, R394.1
unnamed: IC50.15, R407.1
unnamed: IC50.1, R404.1
unnamed: IC50.2, R401.1
unnamed: IC50.3, R398.1
unnamed: IC50.4, R395.1
unnamed: IC50.5, R392.1
unnamed: IC50.6, R389.1
unnamed: IC50.7, R386.1
unnamed: IC51.15, R399.1
unnamed: IC51.1, R397.1
unnamed: IC51.2, R402.1
unnamed: IC51.3, R400.1
unnamed: IC51.4, R405.1
unnamed: IC51.5, R403.1
unnamed: IC51.6, R408.1
unnamed: IC51.7, R406.1
unnamed: IC52.15, R411.1
unnamed: IC52.1, R409.1
unnamed: IC52.2, R414.1
unnamed: IC52.3, R412.1
unnamed: IC52.4, R417.1
unnamed: IC52.5, R415.1
unnamed: IC52.6, R420.1
unnamed: IC52.7, R418.1
unnamed: IC54.15, R423.1
unnamed: IC54.1, R421.1
unnamed: IC54.2, R426.1
unnamed: IC54.3, R424.1
unnamed: IC54.4, R429.1
unnamed: IC54.5, R427.1
unnamed: IC54.6, R432.1
unnamed: IC54.7, R430.1
unnamed: IC53.15, R431.1
unnamed: IC53.1, R428.1
unnamed: IC53.2, R425.1
unnamed: IC53.3, R422.1
unnamed: IC53.4, R419.1
unnamed: IC53.5, R416.1
unnamed: IC53.6, R413.1
unnamed: IC53.7, R410.1
unnamed: IC46.9, IC48.14
unnamed: IC48.9, IC49.14
unnamed: IC49.9, IC51.14
unnamed: IC51.9, IC52.14
unnamed: IC52.9, IC54.14
unnamed: IC53.14, IC54.9
unnamed: IC50.14, IC53.9
unnamed: IC47.14, IC50.9
unnamed: IC46.14, U6.D11
unnamed: S6.1, S6.2, U6.D3
unnamed: LED145.C@1, R433.2
unnamed: LED145.C@3, R434.2
unnamed: LED145.C@4, R435.2
unnamed: LED146.C@1, R436.2
unnamed: LED146.C@3, R437.2
unnamed: LED146.C@4, R438.2
unnamed: LED147.C@1, R439.2
unnamed: LED147.C@3, R440.2
unnamed: LED147.C@4, R441.2
unnamed: LED148.C@1, R442.2
unnamed: LED148.C@3, R443.2
unnamed: LED148.C@4, R444.2
unnamed: LED149.C@1, R445.2
unnamed: LED149.C@3, R446.2
unnamed: LED149.C@4, R447.2
unnamed: LED150.C@1, R448.2
unnamed: LED150.C@3, R449.2
unnamed: LED150.C@4, R450.2
unnamed: LED151.C@1, R451.2
unnamed: LED151.C@3, R452.2
unnamed: LED151.C@4, R453.2
unnamed: LED152.C@1, R454.2
unnamed: LED152.C@3, R455.2
unnamed: LED152.C@4, R456.2
unnamed: LED153.C@1, R457.2
unnamed: LED153.C@3, R458.2
unnamed: LED153.C@4, R459.2
unnamed: LED154.C@1, R460.2
unnamed: LED154.C@3, R461.2
unnamed: LED154.C@4, R462.2
unnamed: LED155.C@1, R463.2
unnamed: LED155.C@3, R464.2
unnamed: LED155.C@4, R465.2
unnamed: LED156.C@1, R466.2
unnamed: LED156.C@3, R467.2
unnamed: LED156.C@4, R468.2
unnamed: LED157.C@1, R469.2
unnamed: LED157.C@3, R470.2
unnamed: LED157.C@4, R471.2
unnamed: LED158.C@1, R472.2
unnamed: LED158.C@3, R473.2
unnamed: LED158.C@4, R474.2
unnamed: LED159.C@1, R475.2
unnamed: LED159.C@3, R476.2
unnamed: LED159.C@4, R477.2
unnamed: LED160.C@1, R478.2
unnamed: LED160.C@3, R479.2
unnamed: LED160.C@4, R480.2
unnamed: LED161.C@1, R481.2
unnamed: LED161.C@3, R482.2
unnamed: LED161.C@4, R483.2
unnamed: LED162.C@1, R484.2
unnamed: LED162.C@3, R485.2
unnamed: LED162.C@4, R486.2
unnamed: LED163.C@1, R487.2
unnamed: LED163.C@3, R488.2
unnamed: LED163.C@4, R489.2
unnamed: LED164.C@1, R490.2
unnamed: LED164.C@3, R491.2
unnamed: LED164.C@4, R492.2
unnamed: LED165.C@1, R493.2
unnamed: LED165.C@3, R494.2
unnamed: LED165.C@4, R495.2
unnamed: LED166.C@1, R496.2
unnamed: LED166.C@3, R497.2
unnamed: LED166.C@4, R498.2
unnamed: LED167.C@1, R499.2
unnamed: LED167.C@3, R500.2
unnamed: LED167.C@4, R501.2
unnamed: LED168.C@1, R502.2
unnamed: LED168.C@3, R503.2
unnamed: LED168.C@4, R504.2
unnamed: IC55.15, R435.1
unnamed: IC55.1, R433.1
unnamed: IC55.2, R438.1
unnamed: IC55.3, R436.1
unnamed: IC55.4, R441.1
unnamed: IC55.5, R439.1
unnamed: IC55.6, R444.1
unnamed: IC55.7, R442.1
unnamed: IC57.15, R447.1
unnamed: IC57.1, R445.1
unnamed: IC57.2, R450.1
unnamed: IC57.3, R448.1
unnamed: IC57.4, R453.1
unnamed: IC57.5, R451.1
unnamed: IC57.6, R456.1
unnamed: IC57.7, R454.1
unnamed: IC56.15, R455.1
unnamed: IC56.1, R452.1
unnamed: IC56.2, R449.1
unnamed: IC56.3, R446.1
unnamed: IC56.4, R443.1
unnamed: IC56.5, R440.1
unnamed: IC56.6, R437.1
unnamed: IC56.7, R434.1
unnamed: IC58.15, R459.1
unnamed: IC58.1, R457.1
unnamed: IC58.2, R462.1
unnamed: IC58.3, R460.1
unnamed: IC58.4, R465.1
unnamed: IC58.5, R463.1
unnamed: IC58.6, R468.1
unnamed: IC58.7, R466.1
unnamed: IC59.15, R479.1
unnamed: IC59.1, R476.1
unnamed: IC59.2, R473.1
unnamed: IC59.3, R470.1
unnamed: IC59.4, R467.1
unnamed: IC59.5, R464.1
unnamed: IC59.6, R461.1
unnamed: IC59.7, R458.1
unnamed: IC60.15, R471.1
unnamed: IC60.1, R469.1
unnamed: IC60.2, R474.1
unnamed: IC60.3, R472.1
unnamed: IC60.4, R477.1
unnamed: IC60.5, R475.1
unnamed: IC60.6, R480.1
unnamed: IC60.7, R478.1
unnamed: IC61.15, R483.1
unnamed: IC61.1, R481.1
unnamed: IC61.2, R486.1
unnamed: IC61.3, R484.1
unnamed: IC61.4, R489.1
unnamed: IC61.5, R487.1
unnamed: IC61.6, R492.1
unnamed: IC61.7, R490.1
unnamed: IC63.15, R495.1
unnamed: IC63.1, R493.1
unnamed: IC63.2, R498.1
unnamed: IC63.3, R496.1
unnamed: IC63.4, R501.1
unnamed: IC63.5, R499.1
unnamed: IC63.6, R504.1
unnamed: IC63.7, R502.1
unnamed: IC62.15, R503.1
unnamed: IC62.1, R500.1
unnamed: IC62.2, R497.1
unnamed: IC62.3, R494.1
unnamed: IC62.4, R491.1
unnamed: IC62.5, R488.1
unnamed: IC62.6, R485.1
unnamed: IC62.7, R482.1
unnamed: IC55.9, IC57.14
unnamed: IC57.9, IC58.14
unnamed: IC58.9, IC60.14
unnamed: IC60.9, IC61.14
unnamed: IC61.9, IC63.14
unnamed: IC62.14, IC63.9
unnamed: IC59.14, IC62.9
unnamed: IC56.14, IC59.9
unnamed: IC55.14, U7.D11
unnamed: S7.1, S7.2, U7.D3
unnamed: LED169.C@1, R505.2
unnamed: LED169.C@3, R506.2
unnamed: LED169.C@4, R507.2
unnamed: LED170.C@1, R508.2
unnamed: LED170.C@3, R509.2
unnamed: LED170.C@4, R510.2
unnamed: LED171.C@1, R511.2
unnamed: LED171.C@3, R512.2
unnamed: LED171.C@4, R513.2
unnamed: LED172.C@1, R514.2
unnamed: LED172.C@3, R515.2
unnamed: LED172.C@4, R516.2
unnamed: LED173.C@1, R517.2
unnamed: LED173.C@3, R518.2
unnamed: LED173.C@4, R519.2
unnamed: LED174.C@1, R520.2
unnamed: LED174.C@3, R521.2
unnamed: LED174.C@4, R522.2
unnamed: LED175.C@1, R523.2
unnamed: LED175.C@3, R524.2
unnamed: LED175.C@4, R525.2
unnamed: LED176.C@1, R526.2
unnamed: LED176.C@3, R527.2
unnamed: LED176.C@4, R528.2
unnamed: LED177.C@1, R529.2
unnamed: LED177.C@3, R530.2
unnamed: LED177.C@4, R531.2
unnamed: LED178.C@1, R532.2
unnamed: LED178.C@3, R533.2
unnamed: LED178.C@4, R534.2
unnamed: LED179.C@1, R535.2
unnamed: LED179.C@3, R536.2
unnamed: LED179.C@4, R537.2
unnamed: LED180.C@1, R538.2
unnamed: LED180.C@3, R539.2
unnamed: LED180.C@4, R540.2
unnamed: LED181.C@1, R541.2
unnamed: LED181.C@3, R542.2
unnamed: LED181.C@4, R543.2
unnamed: LED182.C@1, R544.2
unnamed: LED182.C@3, R545.2
unnamed: LED182.C@4, R546.2
unnamed: LED183.C@1, R547.2
unnamed: LED183.C@3, R548.2
unnamed: LED183.C@4, R549.2
unnamed: LED184.C@1, R550.2
unnamed: LED184.C@3, R551.2
unnamed: LED184.C@4, R552.2
unnamed: LED185.C@1, R553.2
unnamed: LED185.C@3, R554.2
unnamed: LED185.C@4, R555.2
unnamed: LED186.C@1, R556.2
unnamed: LED186.C@3, R557.2
unnamed: LED186.C@4, R558.2
unnamed: LED187.C@1, R559.2
unnamed: LED187.C@3, R560.2
unnamed: LED187.C@4, R561.2
unnamed: LED188.C@1, R562.2
unnamed: LED188.C@3, R563.2
unnamed: LED188.C@4, R564.2
unnamed: LED189.C@1, R565.2
unnamed: LED189.C@3, R566.2
unnamed: LED189.C@4, R567.2
unnamed: LED190.C@1, R568.2
unnamed: LED190.C@3, R569.2
unnamed: LED190.C@4, R570.2
unnamed: LED191.C@1, R571.2
unnamed: LED191.C@3, R572.2
unnamed: LED191.C@4, R573.2
unnamed: LED192.C@1, R574.2
unnamed: LED192.C@3, R575.2
unnamed: LED192.C@4, R576.2
unnamed: IC64.15, R507.1
unnamed: IC64.1, R505.1
unnamed: IC64.2, R510.1
unnamed: IC64.3, R508.1
unnamed: IC64.4, R513.1
unnamed: IC64.5, R511.1
unnamed: IC64.6, R516.1
unnamed: IC64.7, R514.1
unnamed: IC66.15, R519.1
unnamed: IC66.1, R517.1
unnamed: IC66.2, R522.1
unnamed: IC66.3, R520.1
unnamed: IC66.4, R525.1
unnamed: IC66.5, R523.1
unnamed: IC66.6, R528.1
unnamed: IC66.7, R526.1
unnamed: IC65.15, R527.1
unnamed: IC65.1, R524.1
unnamed: IC65.2, R521.1
unnamed: IC65.3, R518.1
unnamed: IC65.4, R515.1
unnamed: IC65.5, R512.1
unnamed: IC65.6, R509.1
unnamed: IC65.7, R506.1
unnamed: IC67.15, R531.1
unnamed: IC67.1, R529.1
unnamed: IC67.2, R534.1
unnamed: IC67.3, R532.1
unnamed: IC67.4, R537.1
unnamed: IC67.5, R535.1
unnamed: IC67.6, R540.1
unnamed: IC67.7, R538.1
unnamed: IC68.15, R551.1
unnamed: IC68.1, R548.1
unnamed: IC68.2, R545.1
unnamed: IC68.3, R542.1
unnamed: IC68.4, R539.1
unnamed: IC68.5, R536.1
unnamed: IC68.6, R533.1
unnamed: IC68.7, R530.1
unnamed: IC69.15, R543.1
unnamed: IC69.1, R541.1
unnamed: IC69.2, R546.1
unnamed: IC69.3, R544.1
unnamed: IC69.4, R549.1
unnamed: IC69.5, R547.1
unnamed: IC69.6, R552.1
unnamed: IC69.7, R550.1
unnamed: IC70.15, R555.1
unnamed: IC70.1, R553.1
unnamed: IC70.2, R558.1
unnamed: IC70.3, R556.1
unnamed: IC70.4, R561.1
unnamed: IC70.5, R559.1
unnamed: IC70.6, R564.1
unnamed: IC70.7, R562.1
unnamed: IC72.15, R567.1
unnamed: IC72.1, R565.1
unnamed: IC72.2, R570.1
unnamed: IC72.3, R568.1
unnamed: IC72.4, R573.1
unnamed: IC72.5, R571.1
unnamed: IC72.6, R576.1
unnamed: IC72.7, R574.1
unnamed: IC71.15, R575.1
unnamed: IC71.1, R572.1
unnamed: IC71.2, R569.1
unnamed: IC71.3, R566.1
unnamed: IC71.4, R563.1
unnamed: IC71.5, R560.1
unnamed: IC71.6, R557.1
unnamed: IC71.7, R554.1
unnamed: IC64.9, IC66.14
unnamed: IC66.9, IC67.14
unnamed: IC67.9, IC69.14
unnamed: IC69.9, IC70.14
unnamed: IC70.9, IC72.14
unnamed: IC71.14, IC72.9
unnamed: IC68.14, IC71.9
unnamed: IC65.14, IC68.9
unnamed: IC64.14, U8.D11
unnamed: S8.1, S8.2, U8.D3
unnamed: LED193.C@1, R577.2
unnamed: LED193.C@3, R578.2
unnamed: LED193.C@4, R579.2
unnamed: LED194.C@1, R580.2
unnamed: LED194.C@3, R581.2
unnamed: LED194.C@4, R582.2
unnamed: LED195.C@1, R583.2
unnamed: LED195.C@3, R584.2
unnamed: LED195.C@4, R585.2
unnamed: LED196.C@1, R586.2
unnamed: LED196.C@3, R587.2
unnamed: LED196.C@4, R588.2
unnamed: LED197.C@1, R589.2
unnamed: LED197.C@3, R590.2
unnamed: LED197.C@4, R591.2
unnamed: LED198.C@1, R592.2
unnamed: LED198.C@3, R593.2
unnamed: LED198.C@4, R594.2
unnamed: LED199.C@1, R595.2
unnamed: LED199.C@3, R596.2
unnamed: LED199.C@4, R597.2
unnamed: LED200.C@1, R598.2
unnamed: LED200.C@3, R599.2
unnamed: LED200.C@4, R600.2
unnamed: LED201.C@1, R601.2
unnamed: LED201.C@3, R602.2
unnamed: LED201.C@4, R603.2
unnamed: LED202.C@1, R604.2
unnamed: LED202.C@3, R605.2
unnamed: LED202.C@4, R606.2
unnamed: LED203.C@1, R607.2
unnamed: LED203.C@3, R608.2
unnamed: LED203.C@4, R609.2
unnamed: LED204.C@1, R610.2
unnamed: LED204.C@3, R611.2
unnamed: LED204.C@4, R612.2
unnamed: LED205.C@1, R613.2
unnamed: LED205.C@3, R614.2
unnamed: LED205.C@4, R615.2
unnamed: LED206.C@1, R616.2
unnamed: LED206.C@3, R617.2
unnamed: LED206.C@4, R618.2
unnamed: LED207.C@1, R619.2
unnamed: LED207.C@3, R620.2
unnamed: LED207.C@4, R621.2
unnamed: LED208.C@1, R622.2
unnamed: LED208.C@3, R623.2
unnamed: LED208.C@4, R624.2
unnamed: LED209.C@1, R625.2
unnamed: LED209.C@3, R626.2
unnamed: LED209.C@4, R627.2
unnamed: LED210.C@1, R628.2
unnamed: LED210.C@3, R629.2
unnamed: LED210.C@4, R630.2
unnamed: LED211.C@1, R631.2
unnamed: LED211.C@3, R632.2
unnamed: LED211.C@4, R633.2
unnamed: LED212.C@1, R634.2
unnamed: LED212.C@3, R635.2
unnamed: LED212.C@4, R636.2
unnamed: LED213.C@1, R637.2
unnamed: LED213.C@3, R638.2
unnamed: LED213.C@4, R639.2
unnamed: LED214.C@1, R640.2
unnamed: LED214.C@3, R641.2
unnamed: LED214.C@4, R642.2
unnamed: LED215.C@1, R643.2
unnamed: LED215.C@3, R644.2
unnamed: LED215.C@4, R645.2
unnamed: LED216.C@1, R646.2
unnamed: LED216.C@3, R647.2
unnamed: LED216.C@4, R648.2
unnamed: IC73.15, R579.1
unnamed: IC73.1, R577.1
unnamed: IC73.2, R582.1
unnamed: IC73.3, R580.1
unnamed: IC73.4, R585.1
unnamed: IC73.5, R583.1
unnamed: IC73.6, R588.1
unnamed: IC73.7, R586.1
unnamed: IC75.15, R591.1
unnamed: IC75.1, R589.1
unnamed: IC75.2, R594.1
unnamed: IC75.3, R592.1
unnamed: IC75.4, R597.1
unnamed: IC75.5, R595.1
unnamed: IC75.6, R600.1
unnamed: IC75.7, R598.1
unnamed: IC74.15, R599.1
unnamed: IC74.1, R596.1
unnamed: IC74.2, R593.1
unnamed: IC74.3, R590.1
unnamed: IC74.4, R587.1
unnamed: IC74.5, R584.1
unnamed: IC74.6, R581.1
unnamed: IC74.7, R578.1
unnamed: IC76.15, R603.1
unnamed: IC76.1, R601.1
unnamed: IC76.2, R606.1
unnamed: IC76.3, R604.1
unnamed: IC76.4, R609.1
unnamed: IC76.5, R607.1
unnamed: IC76.6, R612.1
unnamed: IC76.7, R610.1
unnamed: IC77.15, R623.1
unnamed: IC77.1, R620.1
unnamed: IC77.2, R617.1
unnamed: IC77.3, R614.1
unnamed: IC77.4, R611.1
unnamed: IC77.5, R608.1
unnamed: IC77.6, R605.1
unnamed: IC77.7, R602.1
unnamed: IC78.15, R615.1
unnamed: IC78.1, R613.1
unnamed: IC78.2, R618.1
unnamed: IC78.3, R616.1
unnamed: IC78.4, R621.1
unnamed: IC78.5, R619.1
unnamed: IC78.6, R624.1
unnamed: IC78.7, R622.1
unnamed: IC79.15, R627.1
unnamed: IC79.1, R625.1
unnamed: IC79.2, R630.1
unnamed: IC79.3, R628.1
unnamed: IC79.4, R633.1
unnamed: IC79.5, R631.1
unnamed: IC79.6, R636.1
unnamed: IC79.7, R634.1
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
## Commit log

2015-08-05 correct led pin to custom shield
2015-08-05 Custom board
    Use this schematic only for the code
2015-08-05 remove unused board
2015-08-05 Add board picture
